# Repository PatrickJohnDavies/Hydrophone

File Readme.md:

# Intro
This project describes the construction of a stereo audio hydrophone system by building upon the hydrophone design from [Sound Sleuth](https://www.youtube.com/watch?v=KQ_KqJDaOM4). 
Major parts of the system are:
- Hydrophone with preampifier
- Amplifier and headphone driver
- Stand for underwater stereo sound seperation 

# Release Notes:
* V0
    * Bug. Instrumentation amplifier (U1, U2) footprint is incorrent. Therefore switched to AD620. Instrumentation amplifiers with this pinout seem have lower bandwidth.
    * Bug. Q2 has its drain and source reversed.

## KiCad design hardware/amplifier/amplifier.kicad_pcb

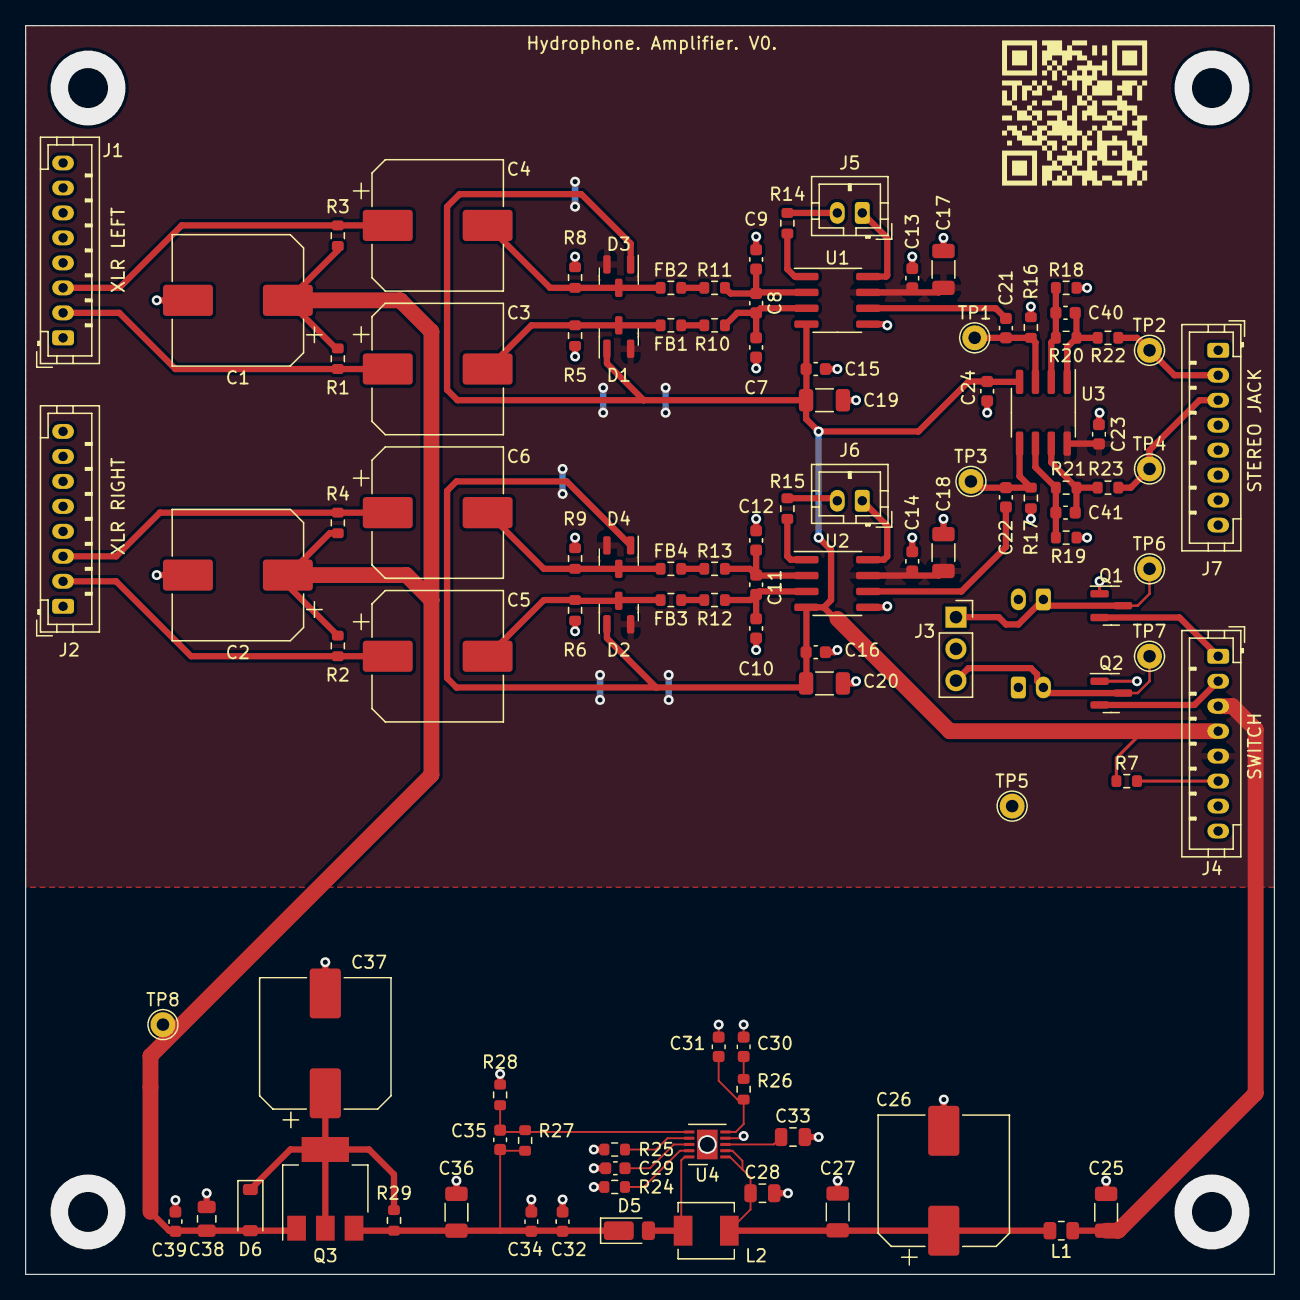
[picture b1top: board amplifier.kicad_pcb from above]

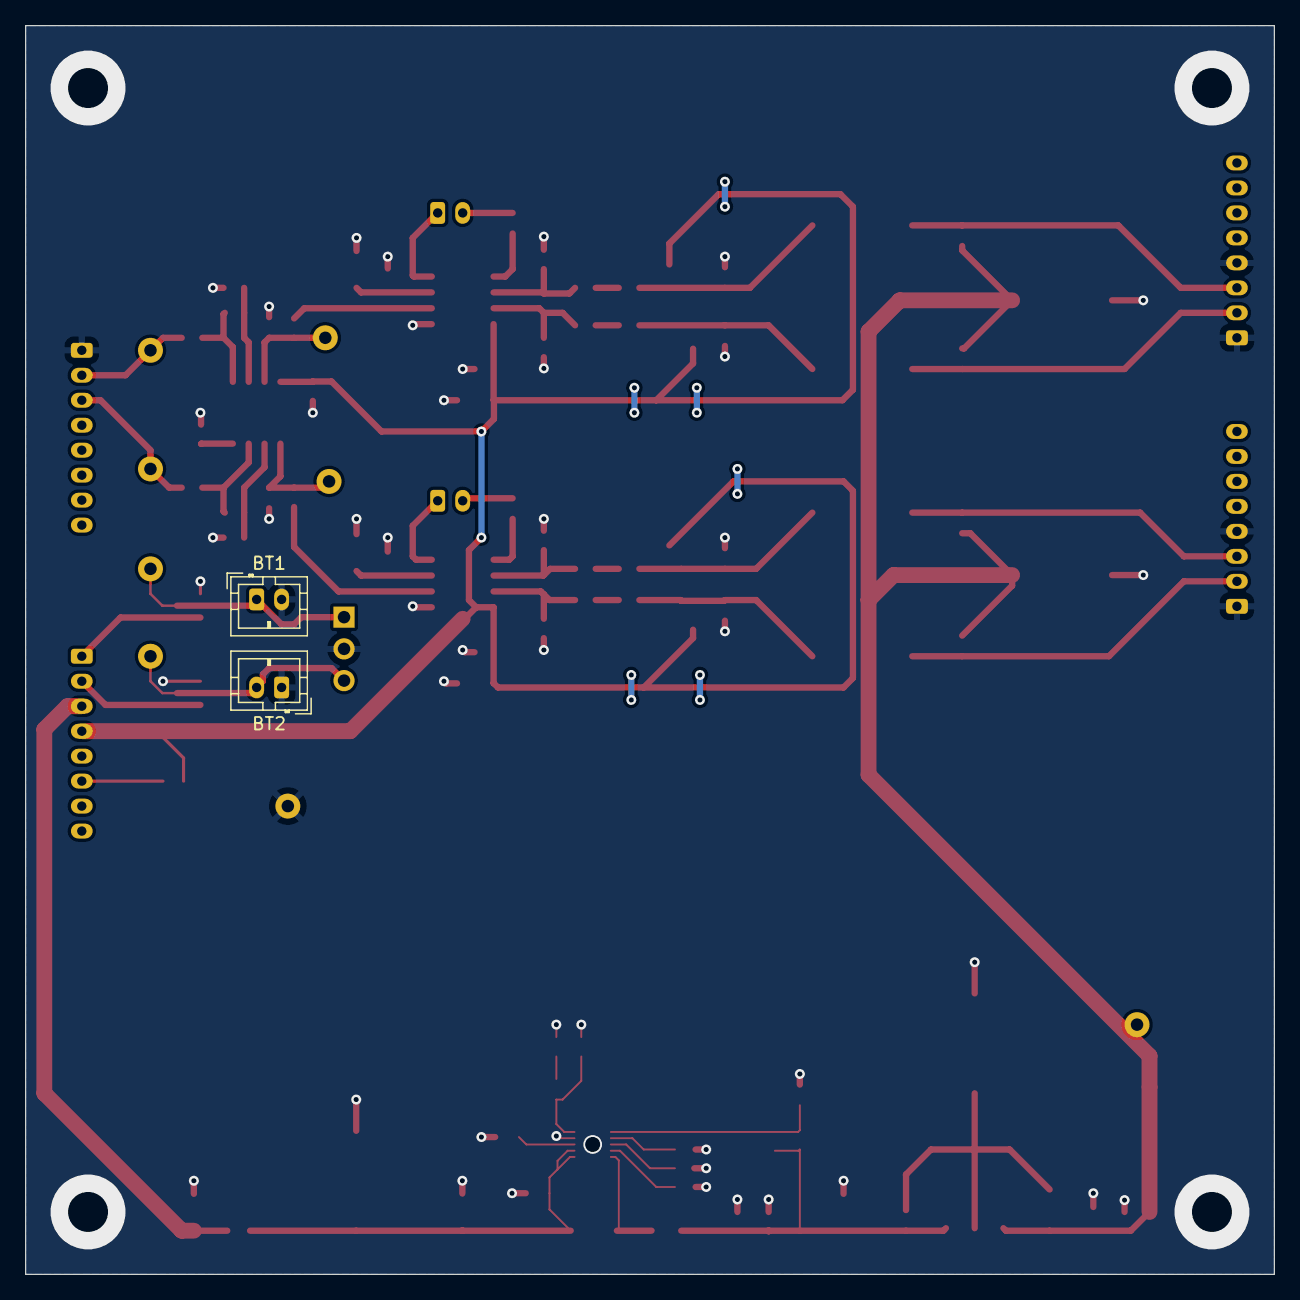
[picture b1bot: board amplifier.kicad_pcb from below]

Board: 2 copper layers, 100.0 x 100.0 mm, 106 parts (2 on the bottom side), 52 nets.

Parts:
BT1, BT2: 9V; JST_PH_B2B-PH-K_1x02_P2.00mm_Vertical
C1, C2, C3, C4, C5, C6, C26: 47u; CP_Elec_10x10
C7, C9, C10, C12, C30: 1n; C_0603_1608Metric
C8, C11, C39: 10n; C_0603_1608Metric
C13, C14, C15, C16, C23, C24, C32, C34: 0.1u; C_0603_1608Metric
C17, C18, C19, C20, C27, C36: 10u; C_1206_3216Metric
C21, C22, C40, C41: DNP; C_0603_1608Metric
C25: 4.7u; C_1206_3216Metric
C28, C33, C38: 1u; C_0805_2012Metric
C29: 0.22u; C_0603_1608Metric
C31: 10p; C_0603_1608Metric
C35: 4.7p; C_0603_1608Metric
C37: 100u; CP_Elec_10x10
D1, D2, D3, D4: BAV199; SOT-23
D5: DFLS260-7; D_PowerDI-123
D6: 1N4148; D_SOD-123
FB1, FB2, FB3, FB4: FerriteBead; R_0603_1608Metric
J1, J2, J4, J7: Conn_01x04; JST_PH_B8B-PH-K_1x08_P2.00mm_Vertical
J3: Conn_01x03; PinSocket_1x03_P2.54mm_Vertical
J5, J6: Conn_01x02; JST_PH_B2B-PH-K_1x02_P2.00mm_Vertical
L1: 0.47u; R_0805_2012Metric
L2: 6.8u; L_Wuerth_74437324068
Q1, Q2: SSM3J338R,LF; SOT-23
Q3: SBCP56-16T1G; SOT-223-3_TabPin2
R1, R2, R3, R4: 6.8k; R_0603_1608Metric
R5, R6, R7, R8, R9: 2.2k; R_0603_1608Metric
R10, R11, R12, R13: 33; R_0603_1608Metric
R14, R15, R20, R21, R22, R23: 0; R_0603_1608Metric
R16, R17, R18, R19: DNP; R_0603_1608Metric
R24: 100k; R_0603_1608Metric
R25, R26: 22k; R_0603_1608Metric
R27: 1M; R_0603_1608Metric
R28: 34.8k; R_0603_1608Metric
R29: 499; R_0603_1608Metric
TP1, TP2, TP3, TP4, TP5, TP6, TP7, TP8: TestPoint; TestPoint_THTPad_D2.0mm_Drill1.0mm
U1, U2: AD8421; SOIC-8_3.9x4.9mm_P1.27mm
U3: OPA1688; SOIC-8_3.9x4.9mm_P1.27mm
U4: LT8362; DFN-10-1EP_3x3mm_P0.5mm_EP1.65x2.38mm

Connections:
+9V: C13.1, C14.1, C17.1, C18.1, C23.1, C25.1, D1.2 (A), D2.2 (A), D3.2 (A), D4.2 (A), J4.3, J4.5, L1.1, U1.7 (V+), U2.7 (V+), U3.8 (V+)
+48V: C1.1, C2.1, C38.1, C39.1, D6.2 (A), Q3.1 (E), R1.2, R2.2, R3.2, R4.2, TP8.1
-9V: C15.1, C16.1, C19.1, C20.1, C24.1, D1.1 (K), D2.1 (K), D3.1 (K), D4.1 (K), J4.4, R7.1, U1.4 (V-), U2.4 (V-), U3.4 (V-)
/HP_Left: J7.2, R22.1, TP2.1
/HP_Right: J7.3, R23.1, TP4.1
/vbat+: BT1.1 (+), J3.1, Q1.3 (D), TP6.1
/vbat-: BT2.2 (-), J3.3, Q2.3 (D), TP7.1
GND: BT1.2 (-), BT2.1 (+), C1.2, C2.2, C7.1, C9.2, C10.1, C12.2, C13.2, C14.2, C15.2, C16.2, C17.2, C18.2, C19.2, C20.2, C23.2, C24.2, C25.2, C26.2, C27.2, C28.2, C29.2, C30.2, C31.2, C32.2, C33.2, C34.2, C36.2, C37.2, C38.2, C39.2, J1.1, J1.4, J2.1, J2.4, J3.2, J7.1, Q1.1 (G), Q2.1 (G), R5.1, R6.1, R8.1, R9.1, R16.2, R17.2, R18.2, R19.2, R24.1, R25.1, R28.1, TP5.1, U1.5 (Ref), U2.5 (Ref), U4.4 (BIAS), U4.11 (GND)
unnamed: C3.2, D1.3 (K), FB1.1, R5.2
unnamed: C4.2, D3.3 (K), FB2.1, R8.2
unnamed: C5.2, D2.3 (K), FB3.1, R6.2
unnamed: C6.2, D4.3 (K), FB4.1, R9.2
unnamed: C21.1, U1.6
unnamed: C22.1, U2.6
unnamed: C30.1, R26.1
unnamed: C40.2, R20.1, R22.2, U3.1
unnamed: C41.2, R21.1, R23.2, U3.7
unnamed: D5.2 (A), L2.2, U4.10 (SW)
unnamed: C32.1, C34.1, C35.1, C36.1, D5.1 (K), Q3.3 (C), R27.2, R29.2
unnamed: C37.1, D6.1 (K), Q3.2 (B), R29.1
unnamed: FB1.2, R10.1
unnamed: FB2.2, R11.1
unnamed: FB3.2, R12.1
unnamed: FB4.2, R13.1
unnamed: C3.1, J1.2, R1.1
unnamed: C4.1, J1.3, R3.1
unnamed: C5.1, J2.2, R2.1
unnamed: C6.1, J2.3, R4.1
unnamed: J4.1, Q1.2 (S)
unnamed: J4.2, Q2.2 (S)
unnamed: J4.6, R7.2
unnamed: J5.1, U1.8 (Rg)
unnamed: J5.2, R14.1
unnamed: J6.1, U2.8 (Rg)
unnamed: J6.2, R15.1
unnamed: R14.2, U1.1 (Rg)
unnamed: R15.2, U2.1 (Rg)
unnamed: C7.2, C8.1, R10.2, U1.3 (+)
unnamed: C8.2, C9.1, R11.2, U1.2 (-)
unnamed: C10.2, C11.1, R12.2, U2.3 (+)
unnamed: C11.2, C12.1, R13.2, U2.2 (-)
unnamed: C21.2, R16.1, TP1.1, U3.3 (+)
unnamed: C40.1, R18.1, R20.2, U3.2 (-)
unnamed: C22.2, R17.1, TP3.1, U3.5 (+)
unnamed: C41.1, R19.1, R21.2, U3.6 (-)
unnamed: C26.1, C27.1, C28.1, L1.2, L2.1, U4.1 (EN/UVLO), U4.2 (Vin)
unnamed: C35.2, R27.1, R28.2, U4.6 (FBX)
unnamed: C33.1, U4.3 (INTVcc)
unnamed: R25.2, U4.7 (RT)
unnamed: C29.1, U4.8 (SS)
unnamed: R24.2, U4.9 (SYNC/MODE)
unnamed: C31.1, R26.2, U4.5 (VC)

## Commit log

2025-05-13 Add beach audio recording
